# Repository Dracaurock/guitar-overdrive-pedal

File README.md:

# Guitar overdrive pedal

An overdrive pedal for electric guitar, designed in KiCad and simulated with ngspice. I built it for the end-of-year
project of my first year of the BUT in Networks & Telecommunications (IUT Auxerre, June 2024), then soldered and
tested it on a real PCB.

The design follows the classic Tube Screamer architecture. ElectroSmash has a
[detailed analysis of the original circuit](https://electrosmash.com/tube-screamer-analysis). I rebuilt it with
parts I could find at school: TL081 op-amps instead of the JRC4558, 2N2222 transistors instead of the 2SC1815, and
1N914 diodes instead of the MA150.

## How it works

The signal goes through five blocks, each one marked on the schematic:

1. **Input buffer.** Q1 (2N2222) is an emitter follower. It gives the guitar a high input impedance so the pickups
   are not loaded.
2. **Gain stage.** U2 (TL081) is a non-inverting amplifier. Two 1N914 diodes in anti-parallel in its feedback loop
   clip the signal softly, which creates the overdrive sound. RV1 sets the amount of distortion.
3. **Tone stage.** U1 (TL081) with RV2 sets how much treble goes through.
4. **Level and output buffer.** RV3 sets the output volume, and Q2 (2N2222) drives the output.
5. **Power supply.** The pedal runs from a 9 V supply on J1 (XT30 connector). R1 and R2 make a 4.5 V reference
   (VAA) so the op-amps can swing around half the supply, and C17 and C10 filter the rails.

## Simulation

The schematic is set up for the KiCad simulator (ngspice): a 20 mV, 440 Hz sine source as the guitar
(`Vinput1`), and a transient analysis `.tran 10u 50m`. The 2N2222 model is written directly in the schematic
(`.model Q2N2222 npn (bf=350)`).

The TL081 and 1N914 models are not in this repository because they belong to their manufacturers. To run the
simulation, download them and place them in `hardware/` with these names:

- `TL081.301`: TL081 PSpice model from [Texas Instruments](https://www.ti.com/product/TL081)
- `1N914.LIB`: 1N914 SPICE model (from the manufacturer of your diode, for example onsemi)

Run an operating-point analysis first to check the DC voltages before the transient analysis.

## PCB

Single board with through-hole parts only (DIP-8 op-amps, TO-92 transistors, axial resistors), so it can be
soldered by hand.

Exports in `docs/`: schematic (PDF and SVG), PCB layers (SVG), 3D view and bill of materials (`bom.csv`).

## Known issues

This was a first-year student project. The KiCad checks still report a few real problems to fix before ordering a
new board: 7 dangling track ends, 1 copper-to-edge clearance error, some silkscreen overlaps, and a few pins flagged
as not driven in the schematic. Most of the other warnings come from library differences between KiCad versions.

## Files

```
hardware/   KiCad project (open overdrive-pedal.kicad_pro with KiCad 8 or later)
docs/       schematic and PCB exports, bill of materials
```

## Author

Antoine Blondeau, now an embedded systems engineering student at ENSTA.

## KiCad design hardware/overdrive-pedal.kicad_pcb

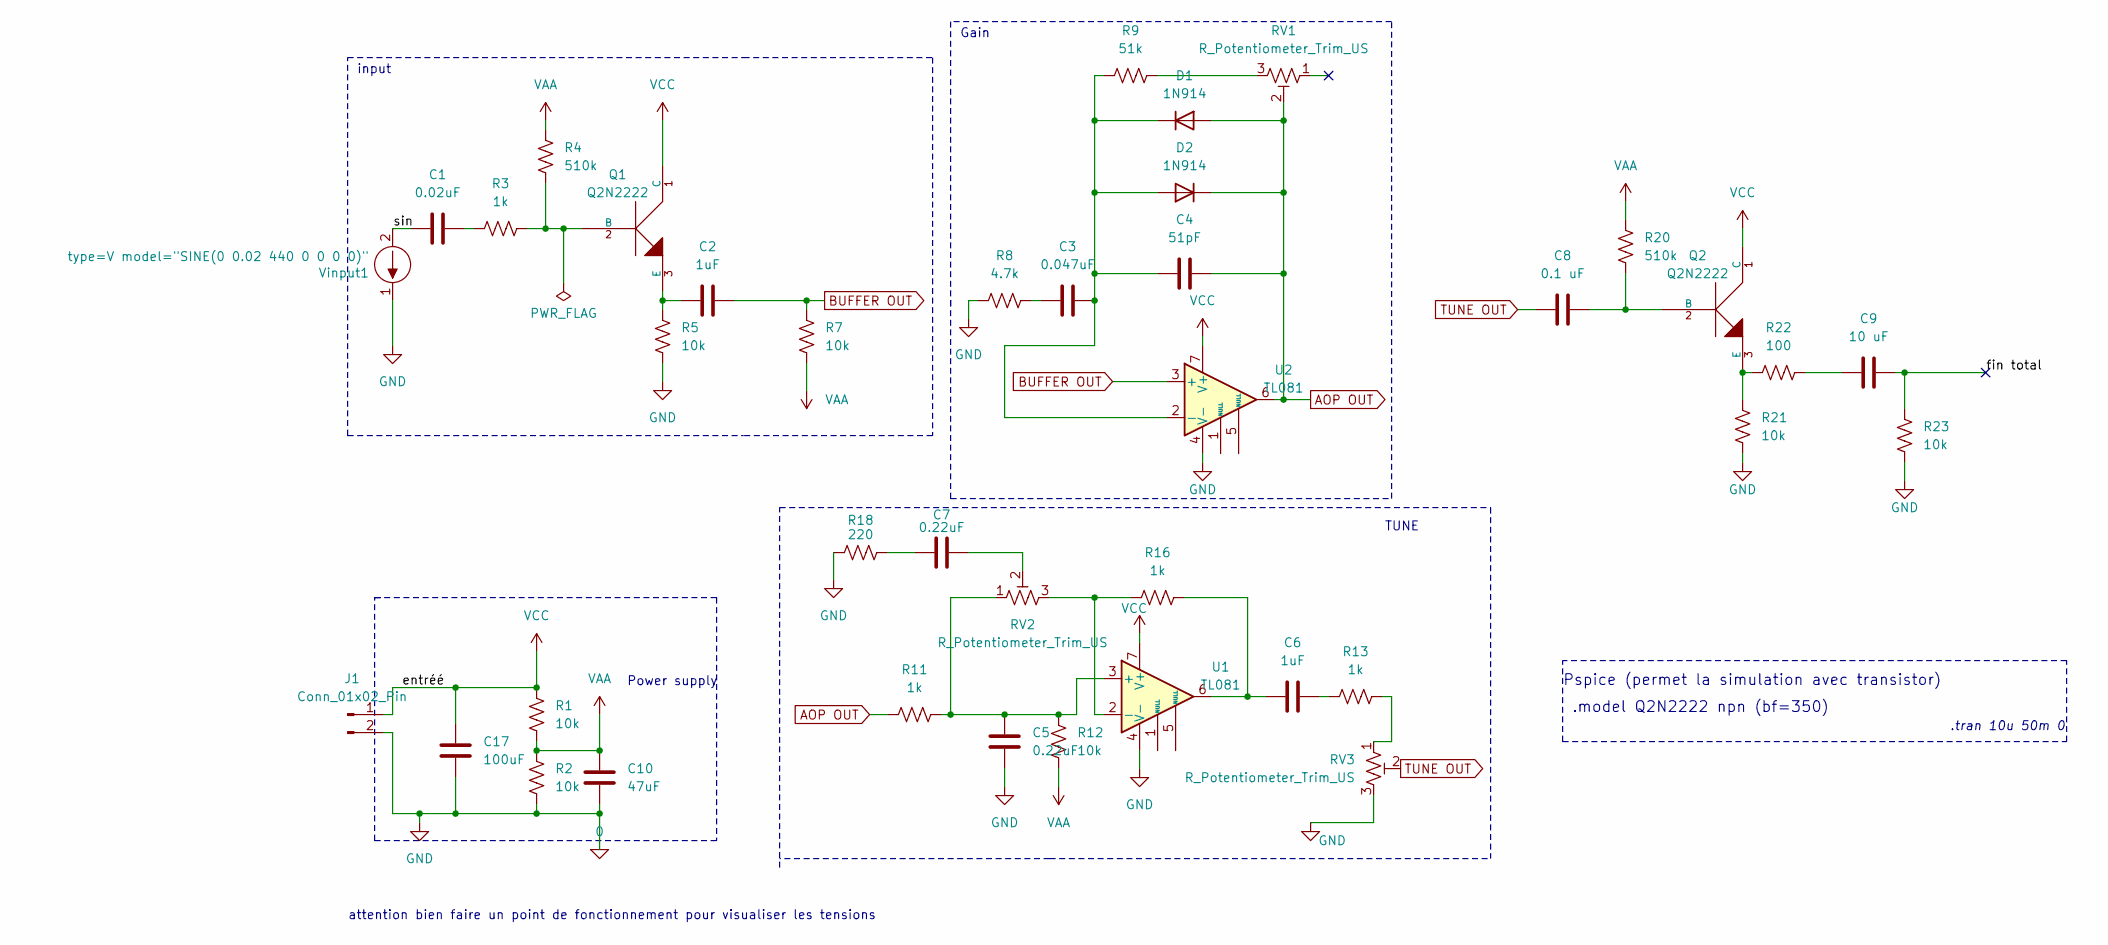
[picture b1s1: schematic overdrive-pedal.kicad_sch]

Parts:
C1: 0.02uF; C_Disc_D8.0mm_W5.0mm_P5.00mm
C2, C6: 1uF; C_Disc_D8.0mm_W5.0mm_P5.00mm
C3: 0.047uF; C_Disc_D8.0mm_W5.0mm_P5.00mm
C4: 51pF; C_Disc_D8.0mm_W5.0mm_P5.00mm
C5, C7: 0.22uF; C_Disc_D8.0mm_W5.0mm_P5.00mm
C8: 0.1 uF; C_Disc_D8.0mm_W5.0mm_P5.00mm
C9: 10 uF; C_Disc_D8.0mm_W5.0mm_P5.00mm
C10: 47uF; C_Disc_D8.0mm_W5.0mm_P5.00mm
C17: 100uF; C_Disc_D8.0mm_W5.0mm_P5.00mm
D1, D2: 1N914; D_DO-35_SOD27_P7.62mm_Horizontal
J1: Conn_01x02_Pin; AMASS_XT30UPB-F_1x02_P5.0mm_Vertical
Q1, Q2: Q2N2222; TO-92
R1, R2, R5, R7, R12, R21, R23: 10k; R_Axial_DIN0309_L9.0mm_D3.2mm_P12.70mm_Horizontal
R3, R11, R13, R16: 1k; R_Axial_DIN0309_L9.0mm_D3.2mm_P12.70mm_Horizontal
R4, R20: 510k; R_Axial_DIN0309_L9.0mm_D3.2mm_P12.70mm_Horizontal
R8: 4.7k; R_Axial_DIN0309_L9.0mm_D3.2mm_P12.70mm_Horizontal
R9: 51k; R_Axial_DIN0309_L9.0mm_D3.2mm_P12.70mm_Horizontal
R18: 220; R_Axial_DIN0309_L9.0mm_D3.2mm_P12.70mm_Horizontal
R22: 100; R_Axial_DIN0309_L9.0mm_D3.2mm_P12.70mm_Horizontal
RV1, RV2, RV3: R_Potentiometer_Trim_US; Potentiometer_Alps_RK163_Single_Horizontal
U1, U2: TL081; DIP-8_W7.62mm
Vinput1: type=V model="SINE(0 0.02 440 0 0 0 0)"

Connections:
0: C5.1, C10.2, C17.2, J1.2, R2.2, R5.2, R8.1, R18.1, R21.1, R23.1, RV3.3, U1.4 (V-), U2.4 (V-), Vinput1.1
/fin total: C9.2, R23.2
/sin: C1.1, Vinput1.2
AOP OUT: C4.2, D1.2 (A), D2.1 (K), R11.1, RV1.2, U2.6
BUFFER OUT: C2.2, R7.2, U2.3 (+)
unnamed: C1.2, R3.1
unnamed: C3.1, R8.2
unnamed: C6.1, R16.2, U1.6
unnamed: C6.2, R13.1
unnamed: C7.1, R18.2
unnamed: C7.2, RV2.2
unnamed: C9.1, R22.1
unnamed: C3.2, C4.1, D1.1 (K), D2.2 (A), R9.1, U2.2 (-)
unnamed: Q1.2 (B), R3.2, R4.2
unnamed: C2.1, Q1.3 (E), R5.1
unnamed: C8.2, Q2.2 (B), R20.1
unnamed: Q2.3 (E), R21.2, R22.2
unnamed: R9.2, RV1.3
unnamed: R13.2, RV3.1
unnamed: C5.2, R11.2, R12.2, RV2.1, U1.3 (+)
unnamed: R16.1, RV2.3, U1.2 (-)
TUNE OUT: C8.1, RV3.2
VAA: C10.1, R1.2, R2.1, R4.1, R7.1, R12.1, R20.2
VCC: C17.1, J1.1, Q1.1 (C), Q2.1 (C), R1.1, U1.7 (V+), U2.7 (V+)

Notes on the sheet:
Gain
attention bien faire un point de fonctionnement pour visualiser les tensions
Power supply
.model Q2N2222 npn (bf=350)
input
TUNE
.tran 10u 50m 0
Pspice (permet la simulation avec transistor)

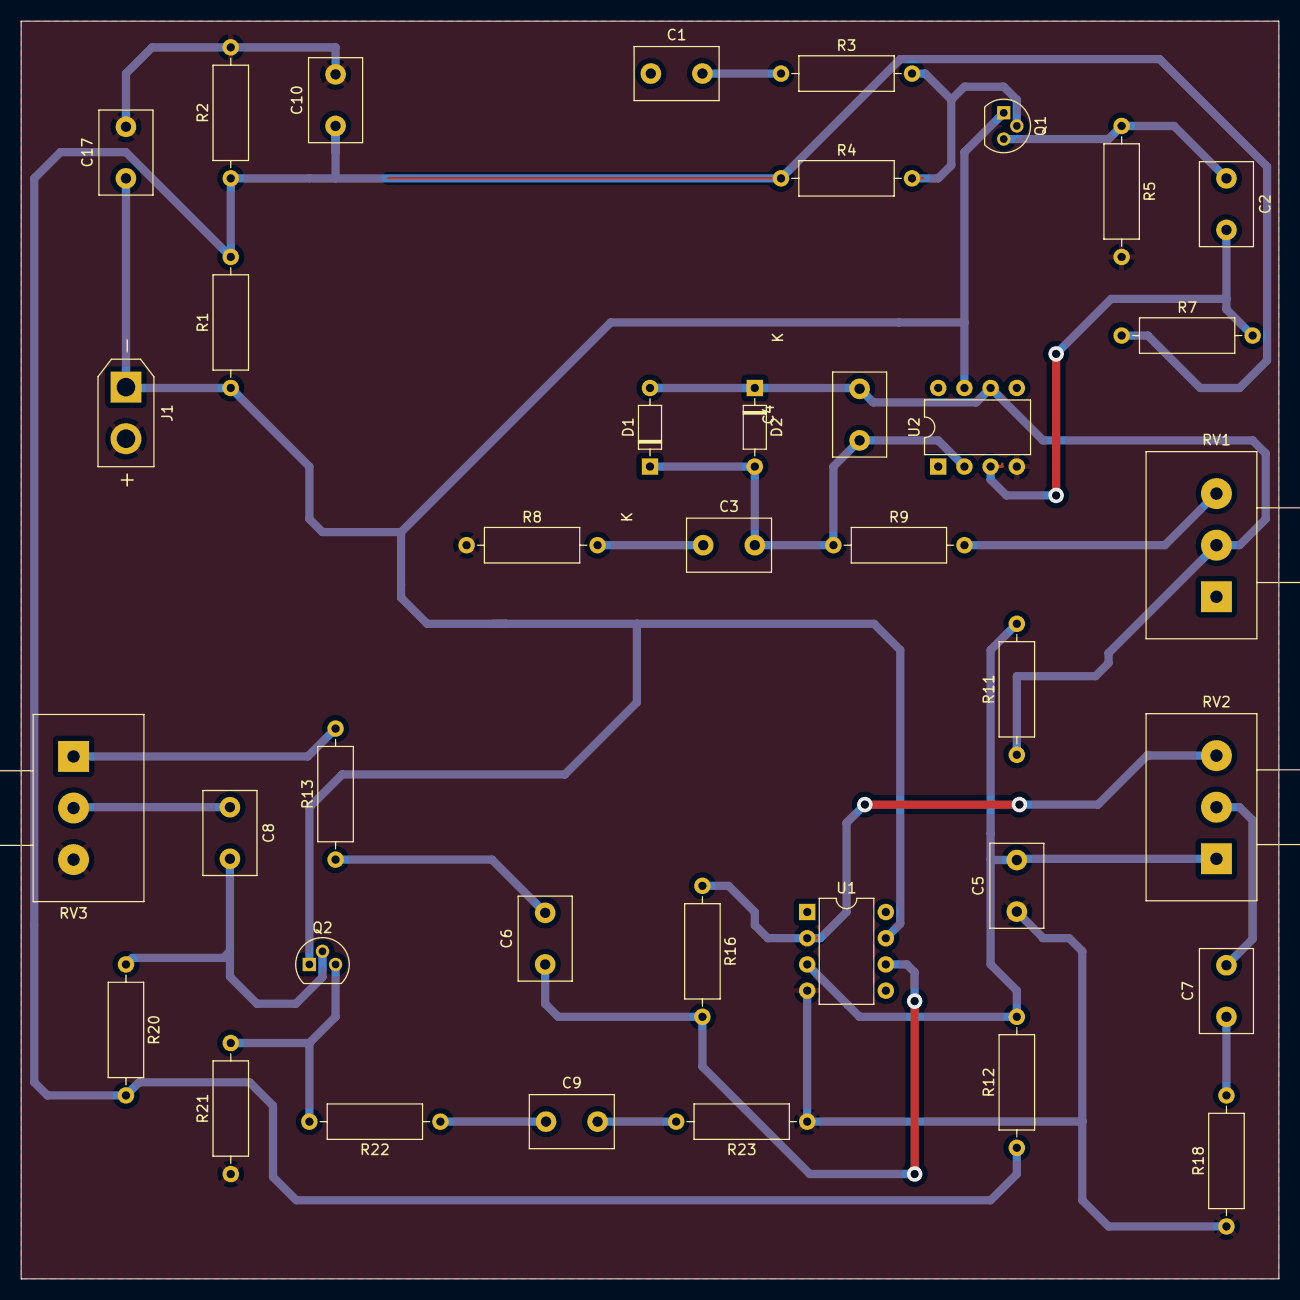
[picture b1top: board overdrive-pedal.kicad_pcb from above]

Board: 2 copper layers, 121.9 x 121.9 mm, 38 parts (0 on the bottom side), 23 nets.

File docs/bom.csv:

"Refs","Value","Footprint","Qty","DNP"
"C1","0.02uF","Capacitor_THT:C_Disc_D8.0mm_W5.0mm_P5.00mm","1",""
"C2","1uF","Capacitor_THT:C_Disc_D8.0mm_W5.0mm_P5.00mm","1",""
"C3","0.047uF","Capacitor_THT:C_Disc_D8.0mm_W5.0mm_P5.00mm","1",""
"C4","51pF","Capacitor_THT:C_Disc_D8.0mm_W5.0mm_P5.00mm","1",""
"C5","0.22uF","Capacitor_THT:C_Disc_D8.0mm_W5.0mm_P5.00mm","1",""
"C6","1uF","Capacitor_THT:C_Disc_D8.0mm_W5.0mm_P5.00mm","1",""
"C7","0.22uF","Capacitor_THT:C_Disc_D8.0mm_W5.0mm_P5.00mm","1",""
"C8","0.1 uF","Capacitor_THT:C_Disc_D8.0mm_W5.0mm_P5.00mm","1",""
"C9","10 uF","Capacitor_THT:C_Disc_D8.0mm_W5.0mm_P5.00mm","1",""
"C10","47uF","Capacitor_THT:C_Disc_D8.0mm_W5.0mm_P5.00mm","1",""
"C17","100uF","Capacitor_THT:C_Disc_D8.0mm_W5.0mm_P5.00mm","1",""
"D1","1N914","Diode_THT:D_DO-35_SOD27_P7.62mm_Horizontal","1",""
"D2","1N914","Diode_THT:D_DO-35_SOD27_P7.62mm_Horizontal","1",""
"J1","Conn_01x02_Pin","Connector_AMASS:AMASS_XT30UPB-F_1x02_P5.0mm_Vertical","1",""
"Q1","Q2N2222","Package_TO_SOT_THT:TO-92","1",""
"Q2","Q2N2222","Package_TO_SOT_THT:TO-92","1",""
"R1","10k","Resistor_THT:R_Axial_DIN0309_L9.0mm_D3.2mm_P12.70mm_Horizontal","1",""
"R2","10k","Resistor_THT:R_Axial_DIN0309_L9.0mm_D3.2mm_P12.70mm_Horizontal","1",""
"R3","1k","Resistor_THT:R_Axial_DIN0309_L9.0mm_D3.2mm_P12.70mm_Horizontal","1",""
"R4","510k","Resistor_THT:R_Axial_DIN0309_L9.0mm_D3.2mm_P12.70mm_Horizontal","1",""
"R5","10k","Resistor_THT:R_Axial_DIN0309_L9.0mm_D3.2mm_P12.70mm_Horizontal","1",""
"R7","10k","Resistor_THT:R_Axial_DIN0309_L9.0mm_D3.2mm_P12.70mm_Horizontal","1",""
"R8","4.7k","Resistor_THT:R_Axial_DIN0309_L9.0mm_D3.2mm_P12.70mm_Horizontal","1",""
"R9","51k","Resistor_THT:R_Axial_DIN0309_L9.0mm_D3.2mm_P12.70mm_Horizontal","1",""
"R11","1k","Resistor_THT:R_Axial_DIN0309_L9.0mm_D3.2mm_P12.70mm_Horizontal","1",""
"R12","10k","Resistor_THT:R_Axial_DIN0309_L9.0mm_D3.2mm_P12.70mm_Horizontal","1",""
"R13","1k","Resistor_THT:R_Axial_DIN0309_L9.0mm_D3.2mm_P12.70mm_Horizontal","1",""
"R16","1k","Resistor_THT:R_Axial_DIN0309_L9.0mm_D3.2mm_P12.70mm_Horizontal","1",""
"R18","220","Resistor_THT:R_Axial_DIN0309_L9.0mm_D3.2mm_P12.70mm_Horizontal","1",""
"R20","510k","Resistor_THT:R_Axial_DIN0309_L9.0mm_D3.2mm_P12.70mm_Horizontal","1",""
"R21","10k","Resistor_THT:R_Axial_DIN0309_L9.0mm_D3.2mm_P12.70mm_Horizontal","1",""
"R22","100","Resistor_THT:R_Axial_DIN0309_L9.0mm_D3.2mm_P12.70mm_Horizontal","1",""
"R23","10k","Resistor_THT:R_Axial_DIN0309_L9.0mm_D3.2mm_P12.70mm_Horizontal","1",""
"RV1","R_Potentiometer_Trim_US","Potentiometer_THT:Potentiometer_Alps_RK163_Single_Horizontal","1",""
"RV2","R_Potentiometer_Trim_US","Potentiometer_THT:Potentiometer_Alps_RK163_Single_Horizontal","1",""
"RV3","R_Potentiometer_Trim_US","Potentiometer_THT:Potentiometer_Alps_RK163_Single_Horizontal","1",""
"U1","TL081","Package_DIP:DIP-8_W7.62mm","1",""
"U2","TL081","Package_DIP:DIP-8_W7.62mm","1",""
"Vinput1","type=V model=""SINE(0 0.02 440 0 0 0 0)""","","1",""
